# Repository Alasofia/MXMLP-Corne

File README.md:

# MXMLP-Corne
Corne made with my MXMountLP footprints

If you intend to sell this for profit, please contact me by email or on Discord.
alas@duck.com / @alas.mx

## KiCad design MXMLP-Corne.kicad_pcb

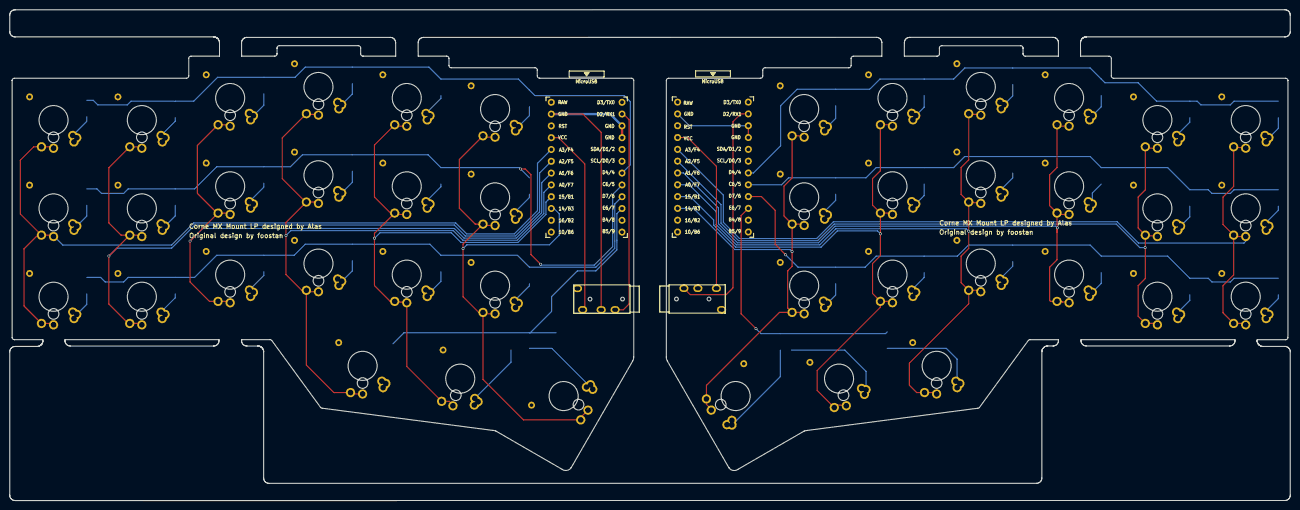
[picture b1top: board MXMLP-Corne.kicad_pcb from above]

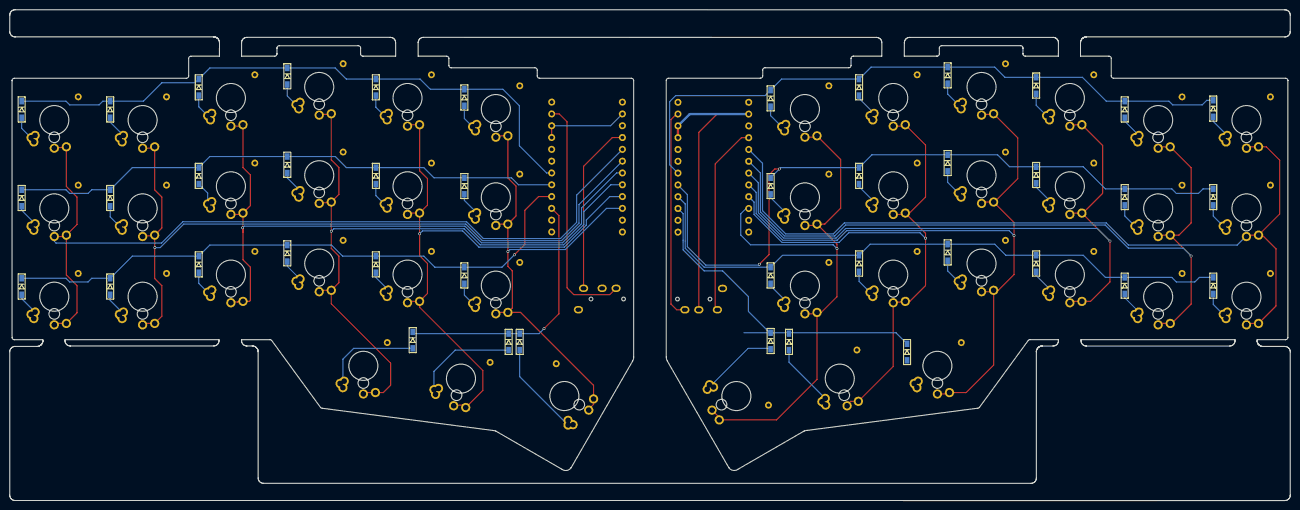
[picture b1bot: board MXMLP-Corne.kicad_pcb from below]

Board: 2 copper layers, 275.5 x 105.6 mm, 88 parts (42 on the bottom side), 68 nets.

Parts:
D1, D2, D3, D4, D5, D6, D7, D8, D9, D10, D11, D12, D13, D14, D15, D16, D17, D18, D19, D20, D21, D22, D23, D24, D25, D26, D27, D28, D29, D30, D31, D32, D33, D34, D35, D36, D37, D38, D39, D40, D41, D42: D; D3_SMD_v2
J1, J2: Conn_01x04_Female; TRRS-PJ-320A
SW1, SW2, SW3, SW4, SW5, SW6, SW7, SW8, SW9, SW10, SW11, SW12, SW13, SW14, SW15, SW16, SW17, SW18, SW19, SW20, SW21, SW22, SW23, SW24, SW25, SW26, SW27, SW28, SW29, SW30, SW31, SW32, SW33, SW34, SW35, SW36, SW37, SW38, SW39, SW40, SW41, SW42: SW_Push; MXMountLP-1U
U1, U2: ProMicro; ProMicro_v3

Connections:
GND: J1.3, J2.3, U1.3, U1.4, U1.23
GNDA: U2.3, U2.4, U2.23
unnamed: D1.2, SW1.2
unnamed: D2.2, SW2.2
unnamed: D3.2, SW3.2
unnamed: D4.2, SW4.2
unnamed: D5.2, SW5.2
unnamed: D6.2, SW6.2
unnamed: D7.2, SW7.2
unnamed: D8.2, SW8.2
unnamed: D9.2, SW9.2
unnamed: D10.2, SW10.2
unnamed: D11.2, SW11.2
unnamed: D12.2, SW12.2
unnamed: D13.2, SW13.2
unnamed: D14.2, SW14.2
unnamed: D15.2, SW15.2
unnamed: D16.2, SW16.2
unnamed: D17.2, SW17.2
unnamed: D18.2, SW18.2
unnamed: D19.2, SW19.2
unnamed: D20.2, SW20.2
unnamed: D21.2, SW21.2
unnamed: D22.2, SW22.2
unnamed: D23.2, SW23.2
unnamed: D24.2, SW24.2
unnamed: D25.2, SW25.2
unnamed: D26.2, SW26.2
unnamed: D27.2, SW27.2
unnamed: D28.2, SW28.2
unnamed: D29.2, SW29.2
unnamed: D30.2, SW30.2
unnamed: D31.2, SW31.2
unnamed: D32.2, SW32.2
unnamed: D33.2, SW33.2
unnamed: D34.2, SW34.2
unnamed: D35.2, SW35.2
unnamed: D36.2, SW36.2
unnamed: D37.2, SW37.2
unnamed: D38.2, SW38.2
unnamed: D39.2, SW39.2
unnamed: D40.2, SW40.2
unnamed: D41.2, SW41.2
unnamed: D42.2, SW42.2
VCC: J1.2, U1.21
VDD: J2.2, U2.21
col0: SW1.1, SW7.1, SW13.1, U1.20
col0_r: SW22.1, SW28.1, SW34.1, U2.20
col1: SW2.1, SW8.1, SW14.1, U1.19
col1_r: SW23.1, SW29.1, SW35.1, U2.19
col2: SW3.1, SW9.1, SW15.1, U1.18
col2_r: SW24.1, SW30.1, SW36.1, U2.18
col3: SW4.1, SW10.1, SW16.1, SW19.1, U1.17
col3_r: SW25.1, SW31.1, SW37.1, SW40.1, U2.17
col4: SW5.1, SW11.1, SW17.1, SW20.1, U1.16
col4_r: SW26.1, SW32.1, SW38.1, SW41.1, U2.16
col5: SW6.1, SW12.1, SW18.1, SW21.1, U1.15
col5_r: SW27.1, SW33.1, SW39.1, SW42.1, U2.15
data: J1.4, U1.2
data_r: J2.4, U2.2
row0: D1.1, D2.1, D3.1, D4.1, D5.1, D6.1, U1.7
row0_r: D22.1, D23.1, D24.1, D25.1, D26.1, D27.1, U2.7
row1: D7.1, D8.1, D9.1, D10.1, D11.1, D12.1, U1.8
row1_r: D28.1, D29.1, D30.1, D31.1, D32.1, D33.1, U2.8
row2: D13.1, D14.1, D15.1, D16.1, D17.1, D18.1, U1.9
row2_r: D34.1, D35.1, D36.1, D37.1, D38.1, D39.1, U2.9
row3: D19.1, D20.1, D21.1, U1.10
row3_r: D40.1, D41.1, D42.1, U2.10

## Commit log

2021-08-26 Probably done?
2021-08-31 Fixed some footprints
